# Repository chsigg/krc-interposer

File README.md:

# KRC Interposer

The KRC Interposer is a hardware intermediary that converts a standard induction stove dial into a closed-loop temperature controller. It is designed for use with Kuhn Rikon Comfort (KRC) cookware, such as the Duromatic pressure cooker or Hotpan. The interposer intercepts the analog signal from the stove’s physical knob, connects to the cookware lid via Bluetooth Low Energy (BLE), and regulates the stove's power output to maintain a target temperature.

The system is built around the Seeed Studio XIAO nRF52840 microcontroller. It is designed to have no effect during standard stove operation, activating only when smart temperature control is initiated.

## Operating Modes

### Wake and Connection
Smart features are triggered by turning the dial to the stove's built-in **Boil Mode** (below 0). The resulting resistance change is detected by a companion PIC microcontroller, which then wakes the XIAO via serial communication (UART RX).

The microcontroller then takes control of the analog switch, routing its own filtered PWM output to the stove in place of the physical dial. It enters a scanning state to locate a Kuhn Rikon Comfort lid via BLE. Upon successful connection, the device emits an audible beep.

### Active Temperature Control
Once connected, the physical dial's positions are repurposed:
*   **Off:** Pauses heating and acts as an "Off" switch.
*   **1 to 9:** Maps to a target temperature range between 30°C and 120°C.

The interposer reads the current temperature from the BLE lid and uses a proportional-predictive thermal model (with feed-forward heat loss compensation) to simulate the required analog voltage to the stove. It automatically utilizes the stove's native hardware boost modes for rapid heating. A slew-rate limiter ensures smooth voltage transitions to prevent hardware faults on the stove's internal controller.

### Safety and Shutdown
*   **Signal Loss:** If the BLE connection drops, the interposer emits a warning beep and eventually reduces stove power to a safe minimum until the connection is restored.
*   **Power Off:** Turning the dial to **Off** initiates a 5-second shutdown timer. After this delay, the XIAO powers down completely, and the analog switch reconnects the physical dial to the stove.

### Telemetry (Optional)
The interposer concurrently operates as a BLE Peripheral. A [companion app](http://github.com/chsigg/krc-app) can connect to receive real-time telemetry, including measured temperature, target temperature, and diagnostic logs.

### Video of the interposer in action

## Hardware Overview

The interposer board acts as a man-in-the-middle interface between a Miele stove and its physical 10kΩ potentiometer dial. It allows a Seeed Studio XIAO nRF52840 to either passively monitor the dial or actively override the signal to control the stove.

### Dial Interface

The physical dial on the stove functions as a potentiometer, outputting a variable analog voltage to the stove's control electronics:

*   **Off:** The signal line is left floating.
*   **1 to 9:** Standard heating power levels.
*   **Below 0 (Boil Mode):** Resistance drops to a minimum. The stove interprets this as a command to apply maximum power for a set duration before returning to the dial's indicated level.
*   **Above 9 (Boost Mode):** Activates discrete high-power boost levels.

### Core Subsystems

*   **Signal Routing (TMUX1119):** A 5V SPDT analog switch toggles the stove's sensor input. In Bypass Mode (default), it connects the stove directly to the physical dial. In Control Mode, it connects the stove to the synthetic control signal.
*   **ADC Sensing:** Voltage dividers (27kΩ / 51kΩ) step the 5V dial and stove signals down to safe 3.3V levels for the XIAO's ADC. High-impedance values limit parasitic draw to ~30µA, as the stove's 5V line is a current-limited sensor reference (max ~1.5mA) and will collapse under standard loads.
*   **Synthetic Signal Generation (TXU0101 & MCP6042):** The XIAO generates a 3.3V PWM signal. A TXU0101 level shifter steps this up to 5V. An RC filter and an MCP6042 micropower op-amp buffer the signal into a clean analog DC voltage for the stove.
*   **Switched Pull-Down:** A pull-down resistor prevents the op-amp input from floating when the dial is turned off. An N-channel MOSFET disconnects this resistor during Bypass Mode to avoid tripping the stove's safety interlocks.
*   **Power Isolation:** The XIAO must be powered independently via USB. The stove's 5V reference rail cannot supply the current required for microcontroller boot or radio transmission.

## Development

The project is built using PlatformIO and the Arduino framework.

### Build
Compile the firmware for the XIAO nRF52840:
```bash
pio run
```

### Testing
Unit tests are implemented with `doctest` and `ArduinoFake` to run the logic modules natively on the host machine.
```bash
pio test -e native
```

## Software Architecture

The firmware enforces strict separation between high-level control logic and hardware interfaces to facilitate native testing.

*   **`StoveSupervisor`:** A state machine managing the high-level operational states (`SCANNING`, `CONNECTED`, `ACTIVE`, `DISCONNECTED`). It handles timers, user feedback, and logic for engaging hardware boost modes.
*   **`ThermalController`:** Implements the closed-loop temperature regulation using a proportional-predictive model and ambient heat loss compensation.
*   **`StoveActuator`:** Translates logical throttle requests into physical PWM signals. It includes a slew-rate limiter (`0.001/ms`) and minimum voltage clamping to maintain hardware stability on the stove's input line.
*   **`TrendAnalyzer`:** Buffers BLE temperature readings to calculate predicted future temperatures (compensating for system thermal lag) and the current rate of change.
*   **`BleThermometer` (BLE Central):** Scans for and connects to supported KRC lids, passing incoming temperature data to the `TrendAnalyzer`.
*   **`BleTelemetry` (BLE Peripheral):** Broadcasts internal state data and buffered logs to connected clients.
*   **Hardware Abstractions:** Interfaces like `DialSensor` and `StoveActuator` or 'Led' decouple the core logic from Arduino-specific functions, allowing execution against mock objects in the test suite.

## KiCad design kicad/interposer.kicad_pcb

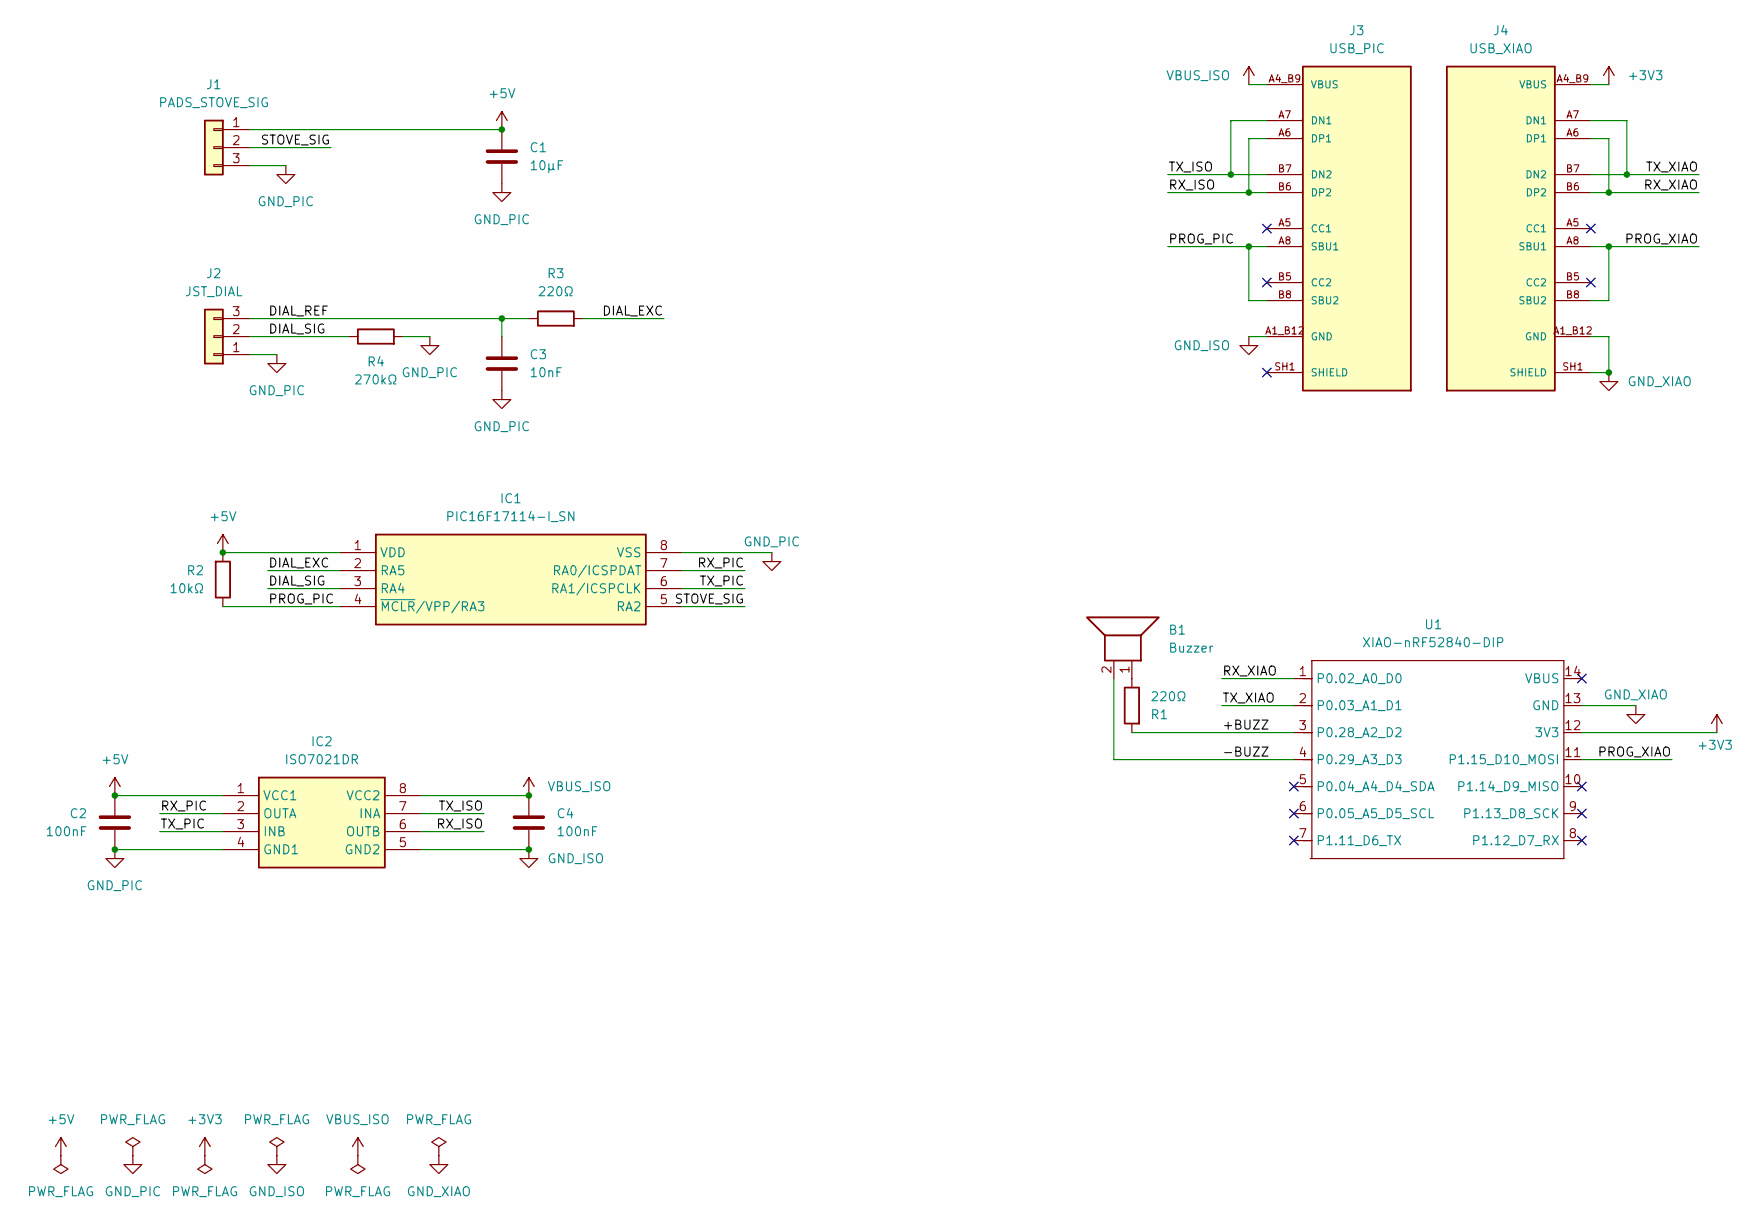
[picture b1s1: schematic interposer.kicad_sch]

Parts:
B1: Buzzer; Buzzer_Murata_PKLCS1212E
C1: 10µF; C_0805_2012Metric_Pad1.18x1.45mm_HandSolder
C2, C4: 100nF; C_0805_2012Metric_Pad1.18x1.45mm_HandSolder
C3: 10nF; C_0805_2012Metric_Pad1.18x1.45mm_HandSolder
IC1: PIC16F17114-I_SN; SOIC-8_3.9x4.9mm_P1.27mm; Manufacturer_Part_Number PIC16F17114-I/SN; Mouser Part Number 579-PIC16F17114-I/SN
IC2: ISO7021DR; SOIC-8_3.9x4.9mm_P1.27mm; Manufacturer_Part_Number ISO7021DR; Mouser Part Number 595-ISO7021DR
J1: PADS_STOVE_SIG; RAST 2.5 Pads
J2: JST_DIAL; JST_XH_S3B-XH-A_1x03_P2.50mm_Horizontal
J3: USB_PIC; SAMESKY_UJ20-C-H-G-SMT-P16-TR; PARTREV 1.0
J4: USB_XIAO; SAMESKY_UJ20-C-H-G-SMT-P16-TR; PARTREV 1.0
R1, R3: 220Ω; R_0805_2012Metric_Pad1.20x1.40mm_HandSolder
R2: 10kΩ; R_0805_2012Metric_Pad1.20x1.40mm_HandSolder
R4: 270kΩ; R_0805_2012Metric_Pad1.20x1.40mm_HandSolder
U1: XIAO-nRF52840-DIP

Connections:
+3V3: J4.A4_B9 (VBUS), J4.B4_A9 (VBUS), U1.12 (3V3)
+5V: C1.1, C2.1, IC1.1 (VDD), IC2.1 (VCC1), J1.1, R2.2
/+BUZZ: R1.2, U1.3 (P0.28_A2_D2)
/-BUZZ: B1.2, U1.4 (P0.29_A3_D3)
/DIAL_EXC: IC1.2 (RA5), R3.2
/DIAL_REF: C3.1, J2.3, R3.1
/DIAL_SIG: IC1.3 (RA4), J2.2, R4.1
/PROG_PIC: IC1.4 (~MCLR/VPP/RA3), J3.A8 (SBU1), J3.B8 (SBU2), R2.1
/PROG_XIAO: J4.A8 (SBU1), J4.B8 (SBU2), U1.11 (P1.15_D10_MOSI)
/RX_ISO: IC2.6 (OUTB), J3.A6 (DP1), J3.B6 (DP2)
/RX_PIC: IC1.7 (RA0/ICSPDAT), IC2.2 (OUTA)
/RX_XIAO: J4.A6 (DP1), J4.B6 (DP2), U1.1 (P0.02_A0_D0)
/STOVE_SIG: IC1.5 (RA2), J1.2
/TX_ISO: IC2.7 (INA), J3.A7 (DN1), J3.B7 (DN2)
/TX_PIC: IC1.6 (RA1/ICSPCLK), IC2.3 (INB)
/TX_XIAO: J4.A7 (DN1), J4.B7 (DN2), U1.2 (P0.03_A1_D1)
GND_ISO: C4.2, IC2.5 (GND2), J3.A1_B12 (GND), J3.A12_B1 (GND)
GND_PIC: C1.2, C2.2, C3.2, IC1.8 (VSS), IC2.4 (GND1), J1.3, J2.1, R4.2
GND_XIAO: J4.A1_B12 (GND), J4.A12_B1 (GND), J4.SH1 (SHIELD), J4.SH2 (SHIELD), J4.SH3 (SHIELD), J4.SH4 (SHIELD), U1.13 (GND)
unnamed: B1.1, R1.1
VBUS_ISO: C4.1, IC2.8 (VCC2), J3.A4_B9 (VBUS), J3.B4_A9 (VBUS)

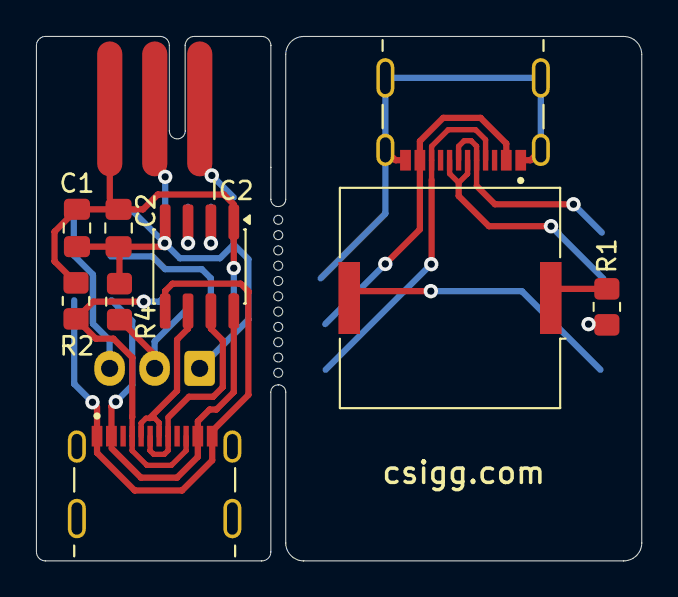
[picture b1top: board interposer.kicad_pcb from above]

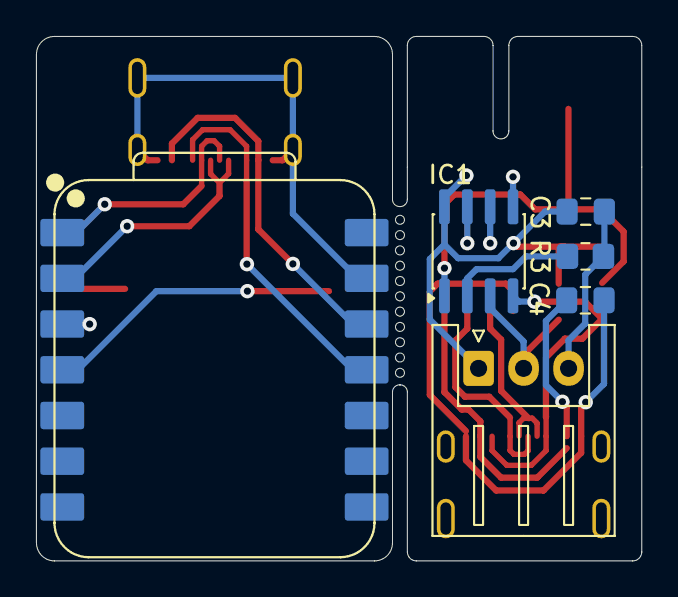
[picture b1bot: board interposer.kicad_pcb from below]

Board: 2 copper layers, 33.6 x 29.1 mm, 16 parts (6 on the bottom side), 21 nets.

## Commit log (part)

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2025-12-01 Create new PlatformIO project.
2025-12-01 Add DigiPot class
2025-12-01 Add StoveDial class
2025-12-01 Add Beeper class
2025-12-01 Add TrendAnalyzer class
2025-12-02 Pass frequency to Buzzer::enable
2025-12-02 Add StoveLevel struct
2025-12-03 Add StoveActuator class
2025-12-03 Rename test files.
2025-12-03 Switch analog reading to float and fix logic
2025-12-03 Add readme and license
2025-12-03 Fix arduino build
2025-12-03 Add Bluetooth and StoveSupervisor
2025-12-03 Some bug fixes but mostly debugging printfs.
2025-12-04 Adding Streaming dependency.
2025-12-04 Resume scanning
2025-12-04 Adding Blinker and improving Bluetooth connection process
2025-12-05 Fix bluetooth connection
2025-12-06 Distinguish 'level' to 'level', 'throttle' and 'position'. Fix Beeper/Blinker states.
2025-12-11 Tee logs to BLEUart
2025-12-12 Allow logging in tested code.
2025-12-12 Add BleTelemetry class
2025-12-12 Allow writing temp measurement.
2025-12-12 Add more logging.
2025-12-12 Request bonding
2025-12-12 Reduce log spew
2025-12-13 Buzzer tuning
2025-12-13 Allow bonding, fix service vs char initialization order
2025-12-13 Improve StoveSupervisor logging
2025-12-14 Log telemetry connect/disconnect
2025-12-14 Make TrendAnalyzer and ThermalController thread safe.
2025-12-14 Only add clients to denylist which refuse to connect. Other failures might be intermittent.
2025-12-14 Fixing boost
2025-12-15 Use LED for digipot testing
2025-12-15 Log when value changed enough since last log.
2025-12-15 Don't connect when dial is on zero.
2025-12-15 NFC: organize main.cpp a bit.
2025-12-15 Store the averaged value in StoveDial.
2025-12-16 Add TrendAnalyzer::clear()
2025-12-16 Don't hide enabled in BleClient, we need it for other states as well.
2025-12-16 Introduce a 'direct' mode before the lid connects where the dial drives the digipot directly.
2025-12-17 Fix millis() overflow issue in Blinker and Beeper.
2025-12-20 Change to i2c potentiometer.
2025-12-20 Don't bypass on timeout, but shut down.
2025-12-20 Mark classes final
2025-12-20 Make denied client list finite and add connecting clients as well.
2025-12-22 Move actuator initialization to setup.
2025-12-22 Add KiCad model
2025-12-23 Update KiCad to two layers
2025-12-24 Don't advertise intermediate temperature when there is no data.
2025-12-26 Use built-in LEDs for feedback.
2025-12-26 Remove shutter client and clean up.
2025-12-26 Fix buzzer.
2025-12-29 Change UX to use auto-mode to change to controlled mode.
2025-12-30 Add a DISCONNECTED state and fix various state transition things.
2025-12-30 Stop beeping when exiting disconnected state.
2025-12-30 Add DFU service.
2026-01-30 Only boost when termperature is 20° below target.
2026-01-30 Hook red led to input reading
2026-01-31 Fix DFU (MTU negotiation) Simplify boost activation
2026-02-02 Adjust BLE power and timings.
2026-02-03 Add poweroff()
2026-03-02 Simplify stove control logic and state machine
    - Refactor StoveActuator to use AnalogWritePin and remove bypass logic.
    - Streamline StoveSupervisor by removing redundant states (SLEEP, COOLDOWN, ACTIVATING).
    - Add power-off callback support to StoveSupervisor.
    - Remove the unused Blinker component.
2026-03-02 Remove green LED when bypass is active
2026-03-02 Remove red LED to show the dial reading
2026-03-03 Move bypass pin and only take over control once lid is connected.
2026-03-03 Add Gemini instructions
2026-03-03 Fix disconnect condition
2026-03-03 Ignore boil and boost dial positions when active
2026-03-03 Add LED feedback
2026-03-03 Add power-on/off beep, remove StoveDial averaging.
2026-03-03 Remove unnecessary calls
2026-03-03 Add ThermalController test
2026-03-03 now -> now_ms
2026-03-04 Move blue led to BleThermometer
2026-03-04 Fix wakup pin choice
2026-03-05 Moving missing temp data to BleThermometer::connected
2026-03-05 Bond with peripheral
2026-03-05 Disable pwm before shutdown
2026-03-06 Slower BLE connection
2026-03-06 Remove Thermometer base class.
2026-03-06 Disconnect BLE when switching to idle.
2026-03-06 Check peer name in connect callback
2026-03-08 Subscribe to temp measurement to keep connection alive.
2026-03-08 Lower trigger threshold and check boil setting during setup()
2026-03-09 Measured ThrottleConfig values
2026-03-11 Remove lid open detection and calculate regression from monotonic series instead.
2026-03-15 Less verbose logging, retries during BLE connection.
2026-03-21 Set power to zero when dial is zero. Plus some printing and formatting changes.
2026-03-21 Active BLE scanning
2026-03-23 Streamline BleThermometer implementation. Remove state, use active scanning and check name in scan response.
2026-03-23 Replace BLEUart with indicated custom service
2026-03-24 Update connection parameters after discovery.
2026-03-24 Add time stamp to logs.
2026-03-24 NFC: some polishing
2026-03-25 Patch around https://github.com/adafruit/Adafruit_nRF52_Arduino/issues/772
2026-03-26 Update telemetry faster
2026-03-28 Always output a minimum stove level.
2026-03-28 Slewed PWM output.
2026-03-29 Update KiCad
2026-03-29 But back indicate callback.
2026-04-24 New hardware revision using a PIC16F.
2026-04-24 Targeted interfaces for dial input and stove output.
2026-04-24 Move slew and bypass mode from XIAO to PIC
    Communication & Safety Refactor:
    - Master-Slave Protocol: The PIC (interposer.c) has been refactored to be a slave device, responding only to packets from the XIAO (except for a one-shot wake-up packet). The XIAO (ArduinoUart.h) is 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
    - Parity Support: Hardware Even Parity is enabled on the XIAO, and software-emulated Even Parity (using 9-bit mode) is implemented on the PIC.
    - Safe Output Logic: The PIC uses a two-state model (MODE_PASSTHROUGH and MODE_OVERRIDE) and enforces that the stove never appears off when the dial is on (clamping override values to a minimum of 25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
    - Shutdown Sequence: The 5-second
2026-04-24 Fix tests
2026-04-27 Improve PIC code
2026-04-30 Add code to program the PIC from the XIAO
2026-04-30 PIC firmware build fixes
2026-04-30 Fix PIC configuration
2026-04-30 Add PIC firmware binary
2026-05-01 Change programmer pin assignment
2026-05-06 Fix programmer build.
2026-05-06 Switch programmer to bit banging.
2026-05-07 PIC firmware fixes
2026-05-07 Update PIC firmware binary
2026-05-07 Swap PIC TX/RX pins
2026-05-09 Interrupt-free firmware
2026-05-09 Program config section as well
2026-05-10 Fix floating tx pin during power-off, waking up the xiao.
2026-05-11 Add PIC UART frame error detection
2026-05-15 Lowering clock to 500kHz, trying to fix Op-Amp output (which is not exposed on the 8-pin variant, but submitting before changing for completeness)
2026-05-16 Connect DAC directly to RA2, without the Op-Amp.
    The 8 pin version does now allow Op-Amp output.
    Some trickery is needed for low vs high DAC ref range.
    Power consumption is still a bit high at 850uA.
2026-05-16 Idle instead of busy loop
2026-05-18 Optimize PIC active power to 338uA using native MFINTOSC (500 kHz) and PMD, refactor Master UART to non-blocking 9600
2026-05-18 Enable PIC Brown-out Reset (BOD) config for essential hardware protection
2026-05-19 Format file (nfc)
2026-05-19 Idle instead of spin-loop, even though it only saves about 20uA
2026-05-20 Fix clock.
    Correct NOSC value for MFINTOSC is 0b011, but that runs at 1.1mA.
    Switched to HFINTOSC again, running at 730uA.
2026-05-27 Run at 31kHz without sleep
